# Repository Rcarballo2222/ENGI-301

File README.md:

# ENGI-301
Various projects for the class: Intro to Practical EE

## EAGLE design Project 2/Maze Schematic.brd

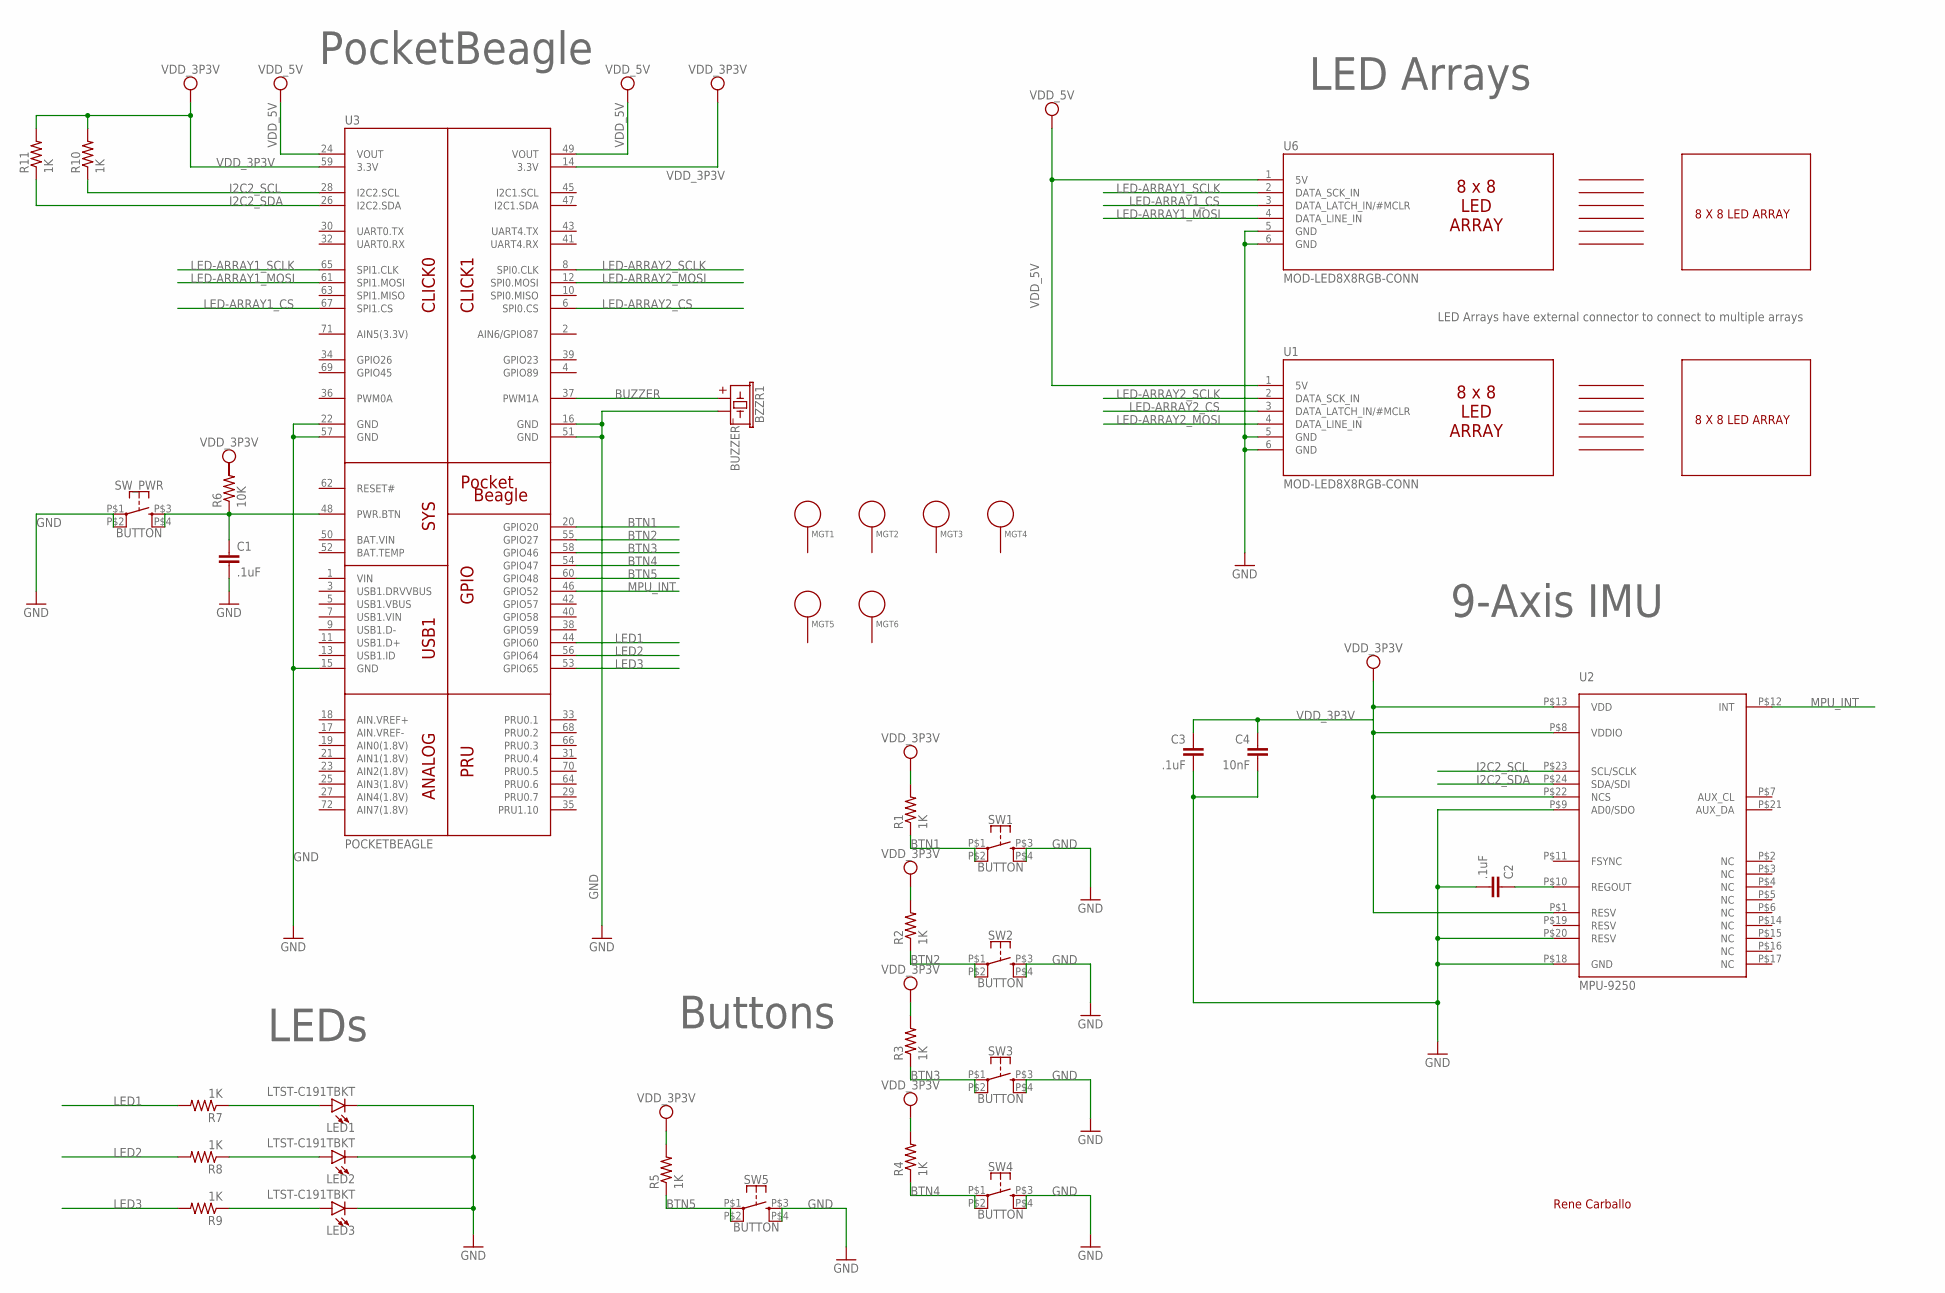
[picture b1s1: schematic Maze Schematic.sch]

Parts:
BZZR1: BUZZER; BUZZER-12MM
C1, C2, C3: .1uF; C0603
C4: 10nF; C0603
LED1, LED2, LED3: LTST-C191TBKT; LED-SMD
MGT1, MGT2, MGT3, MGT4, MGT5, MGT6: MOUNTING_HOLE
R1, R2, R3, R4, R5, R7, R8, R9, R10, R11: 1K; R0603
R6: 10K; R0603
SW1, SW2, SW3, SW4, SW5: BUTTON; BUTTON-11.5X11.7MM
SW_PWR: BUTTON; BUTTON-11.5X11.7MM
U1, U6: MOD-LED8X8RGB-CONN; FE06W
U2: MPU-9250; QFN-3X3MM
U3: POCKETBEAGLE

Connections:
BTN1: R1.1, SW1.P$1 (1), SW1.P$2 (2), U3.20 (GPIO20)
BTN2: R2.1, SW2.P$1 (1), SW2.P$2 (2), U3.55 (GPIO27)
BTN3: R3.1, SW3.P$1 (1), SW3.P$2 (2), U3.58 (GPIO46)
BTN4: R4.1, SW4.P$1 (1), SW4.P$2 (2), U3.54 (GPIO47)
BTN5: R5.1, SW5.P$1 (1), SW5.P$2 (2), U3.60 (GPIO48)
BUZZER: BZZR1.+, U3.37 (PWM1A)
GND: BZZR1.-, C1.2, C2.2, C3.2, C4.2, LED1.C(-), LED2.C(-), LED3.C(-), SW1.P$3 (3), SW1.P$4 (4), SW2.P$3 (3), SW2.P$4 (4), SW3.P$3 (3), SW3.P$4 (4), SW4.P$3 (3), SW4.P$4 (4), SW5.P$3 (3), SW5.P$4 (4), SW_PWR.P$1 (1), SW_PWR.P$2 (2), U1.5 (GND), U1.6 (GND), U2.P$9 (AD0/SDO), U2.P$18 (GND), U2.P$20 (RESV), U3.15 (GND), U3.16 (GND), U3.22 (GND), U3.51 (GND), U3.57 (GND), U6.5 (GND), U6.6 (GND)
I2C2_SCL: R10.1, U2.P$23 (SCL/SCLK), U3.28 (I2C2.SCL)
I2C2_SDA: R11.1, U2.P$24 (SDA/SDI), U3.26 (I2C2.SDA)
LED1: R7.2, U3.44 (GPIO60)
LED2: R8.2, U3.56 (GPIO64)
LED3: R9.2, U3.53 (GPIO65)
LED-ARRAY1_CS: U3.67 (SPI1.CS), U6.3 (DATA_LATCH_IN/#MCLR)
LED-ARRAY1_MOSI: U3.61 (SPI1.MOSI), U6.4 (DATA_LINE_IN)
LED-ARRAY1_SCLK: U3.65 (SPI1.CLK), U6.2 (DATA_SCK_IN)
LED-ARRAY2_CS: U1.3 (DATA_LATCH_IN/#MCLR), U3.6 (SPI0.CS)
LED-ARRAY2_MOSI: U1.4 (DATA_LINE_IN), U3.12 (SPI0.MOSI)
LED-ARRAY2_SCLK: U1.2 (DATA_SCK_IN), U3.8 (SPI0.CLK)
MPU_INT: U2.P$12 (INT), U3.46 (GPIO52)
unnamed: C1.1, R6.1, SW_PWR.P$3 (3), SW_PWR.P$4 (4), U3.48 (PWR.BTN)
unnamed: LED1.A(+), R7.1
unnamed: LED2.A(+), R8.1
unnamed: LED3.A(+), R9.1
REGOUT: C2.1, U2.P$10 (REGOUT)
VDD_3P3V: C3.1, C4.1, R1.2, R2.2, R3.2, R4.2, R5.2, R10.2, R11.2, U2.P$1 (RESV), U2.P$8 (VDDIO), U2.P$13 (VDD), U2.P$22 (NCS), U3.14 (3.3V), U3.59 (3.3V)
VDD_5V: U1.1 (5V), U3.24 (VOUT), U3.49 (VOUT), U6.1 (5V)

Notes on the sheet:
Rene Carballo
LEDs
Buttons
9-Axis IMU
LED Arrays
8 X 8 LED ARRAY
LED Arrays have external connector to connect to multiple arrays
PocketBeagle

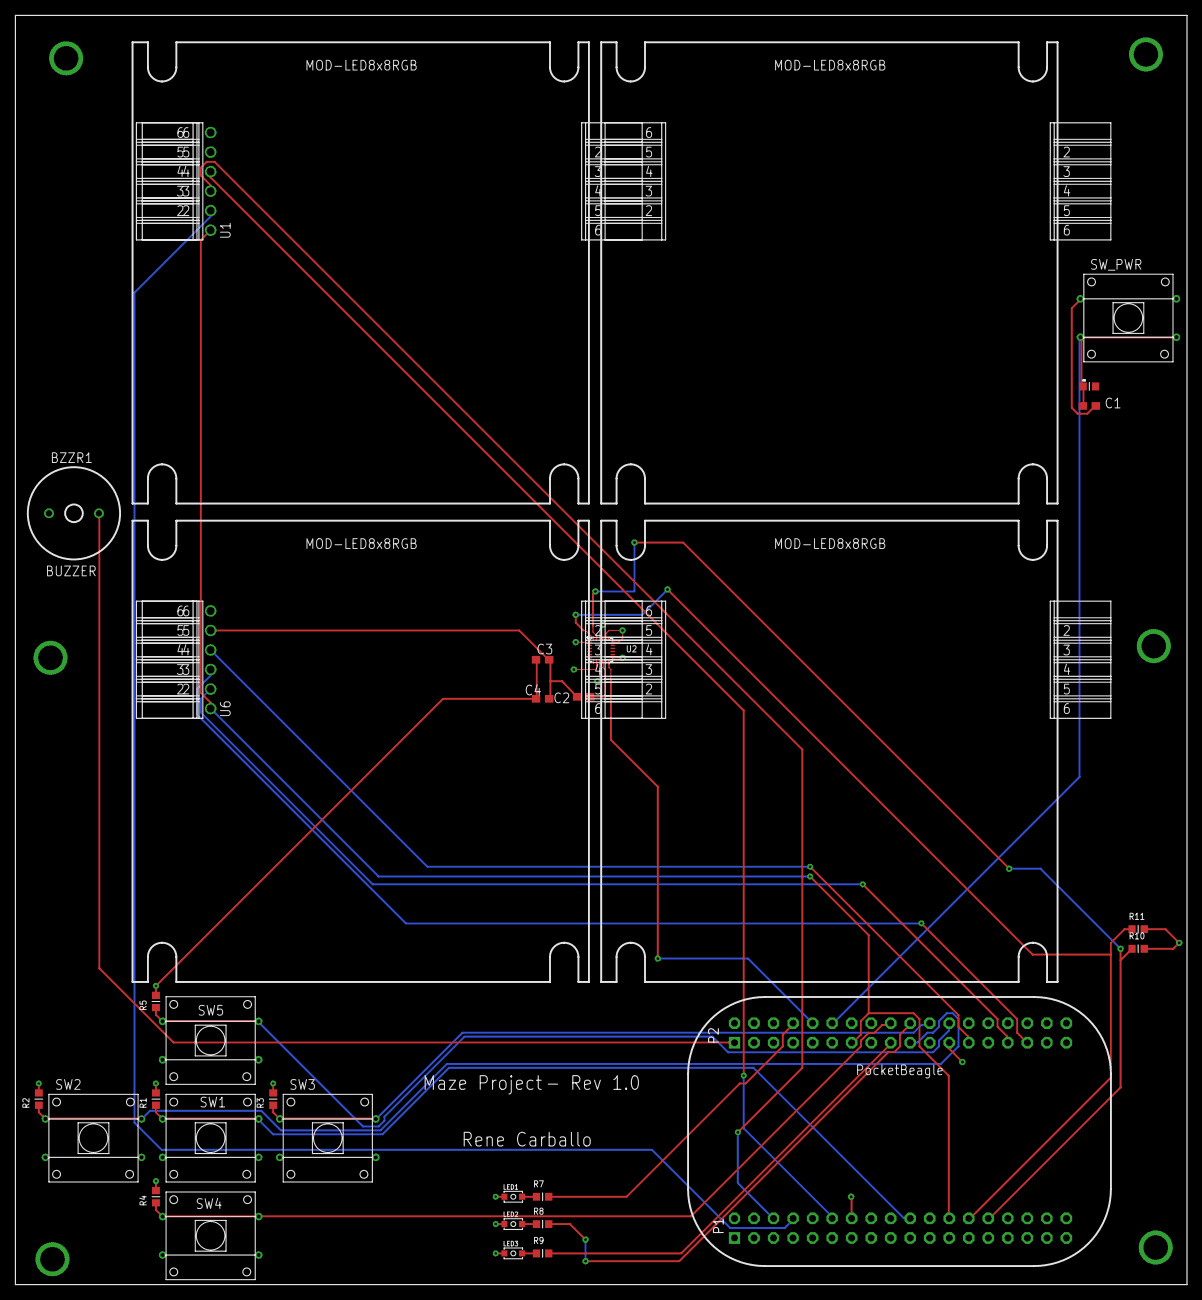
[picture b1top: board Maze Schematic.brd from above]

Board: 4 copper layers, 152.4 x 165.1 mm, 39 parts (0 on the bottom side), 26 nets.

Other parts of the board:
U$1, U$4, U$5, U$6: MOD-LED8X8RGB

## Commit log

2018-04-06 Initial Checkin for WeatherDash
2018-04-06 Updated title + added To do
2018-04-06 Initial Commit for Project 2a
2018-04-06 Updated Description
2018-04-06 Created new buzzer symbol
2018-04-06 Added Buzzer Footprint
2018-04-06 Moved over files from local directory
2018-04-06 Added Other Dependencies
2018-04-06 Removed extra dependencies
2018-04-10 Added Button and LED devices
2018-04-11 Added PocketBeagle and LED Array devices to library
2018-04-11 Added name and value to some packages
2018-04-11 Added Schematic and Board file
2018-04-16 Updated Schematic with missing connections
2018-04-17 Renamed folder to project 2 and updated board layout
2018-04-18 Began routing and updated pocket beagle device
2018-04-19 Completed board routing
2018-04-20 Added Documentation and mounting holes, as well as a pdf version of board and schematic
2018-05-01 Added ST7565 Library with modified example code and library files to work on pocketBeagle
2018-05-03 Updated Readme with instructions
2018-05-04 Reorganized images folder as a python directory and added a create image function
2018-05-04 Testing image usage on display
2018-05-04 Added first weather icons and test images
2018-05-04 Renamed images folder to icons and started initial code for font generator
2018-05-05 Added icons for all main weather conditions
2018-05-05 - Renamed folder back to images as it seemed more appropriate - Made a create_images function that will auto create PIL objects for every image in the images directory
2018-05-05 Changed images to jpg format and updated create_images to support it
2018-05-05 Commented out some stuff
2018-05-06 Added multiple functions for fonts.py and images.py for ease of use
2018-05-07 - Generalized font and image modules to work with any fonts or images - Added more functions to utilize fonts and images easily
2018-05-09 Reorganized file structure, added more functions, and added main run file: WeatherDash.py
2018-05-09 Reorganization
2018-05-15 Reformatting code to work automatically with chrontab
2018-05-16 - Main code now working! - Added splash-screen and debug messages
2018-05-30 Updated Layout, added percent chance of rain, and updated fonts
2018-08-08 Made various improvements and reorganized some things
2018-08-08 Removed unnecessary files from directory
